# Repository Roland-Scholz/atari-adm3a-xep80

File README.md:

# atari-adm3a-xep80
ADM-3A Terminal for ATR8000 and XEP80

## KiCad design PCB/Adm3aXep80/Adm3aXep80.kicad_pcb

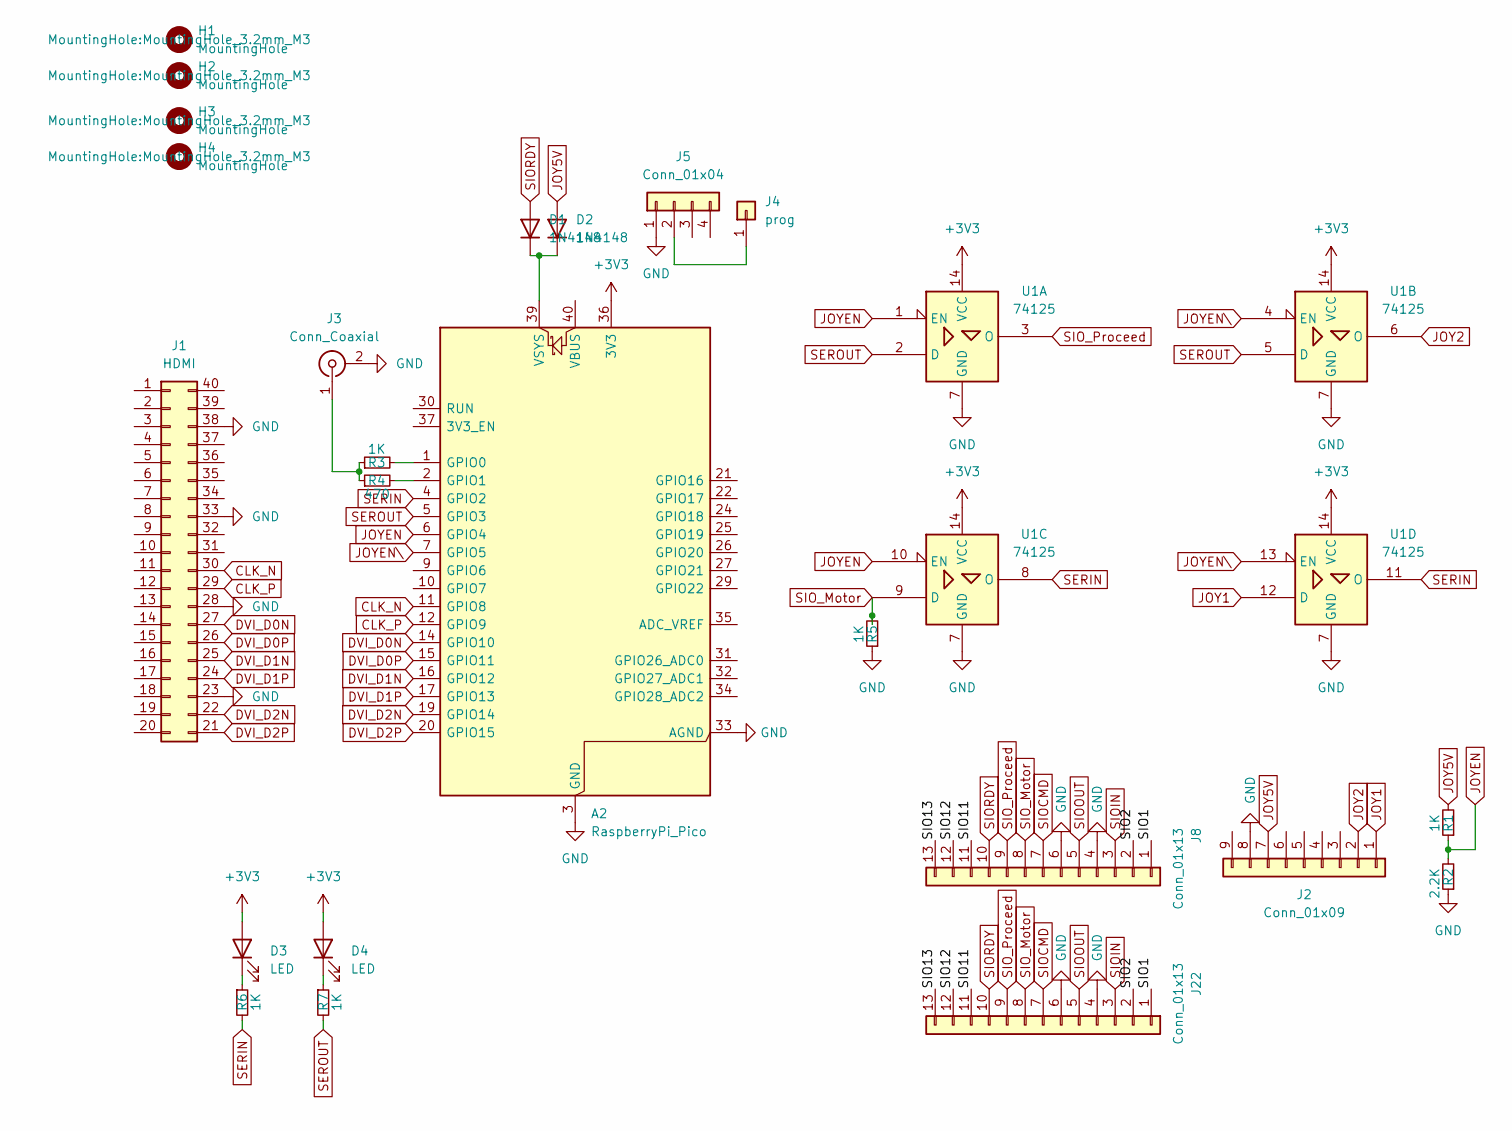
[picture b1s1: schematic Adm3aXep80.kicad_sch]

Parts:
A2: RaspberryPi_Pico; RaspberryPi_Pico_Common_Unspecified
D1, D2: 1N4148; D_DO-35_SOD27_P7.62mm_Horizontal
D3, D4: LED; LED_D3.0mm
H1, H2, H3, H4: MountingHole; MountingHole_3.2mm_M3
J1: HDMI; DIP-40_W25.4mm_Socket_LongPads
J2: Conn_01x09; DSUB-9_Pins_Horizontal_P2.77x2.84mm_EdgePinOffset4.94mm_Hou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
J3: Conn_Coaxial; RCA-Phono_CUI-Devices_RCJ-01X_Horizontal
J4: prog; PinHeader_1x01_P2.54mm_Vertical
J5: Conn_01x04; SW_Tactile_SKHH_Angled
J8, J22: Conn_01x13; SIO_JACK
R1, R3, R5, R6, R7: 1K; R_Axial_DIN0207_L6.3mm_D2.5mm_P10.16mm_Horizontal
R2: 2.2K; R_Axial_DIN0207_L6.3mm_D2.5mm_P10.16mm_Horizontal
R4: 470; R_Axial_DIN0207_L6.3mm_D2.5mm_P10.16mm_Horizontal
U1: 74125; DIP-14_W7.62mm_Socket

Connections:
+3V3: A2.36 (3V3), D3.2 (A), D4.2 (A), U1.14 (VCC)
/SIO1: J8.1, J22.1
/SIO2: J8.2, J22.2
/SIO11: J8.11, J22.11
/SIO12: J8.12, J22.12
/SIO13: J8.13, J22.13
CLK_N: A2.11 (GPIO8), J1.30
CLK_P: A2.12 (GPIO9), J1.29
DVI_D0N: A2.14 (GPIO10), J1.27
DVI_D0P: A2.15 (GPIO11), J1.26
DVI_D1N: A2.16 (GPIO12), J1.25
DVI_D1P: A2.17 (GPIO13), J1.24
DVI_D2N: A2.19 (GPIO14), J1.22
DVI_D2P: A2.20 (GPIO15), J1.21
GND: A2.3 (GND), A2.8 (GND), A2.13 (GND), A2.18 (GND), A2.23 (GND), A2.28 (GND), A2.33 (AGND), A2.38 (GND), J1.23, J1.28, J1.33, J1.38, J2.8, J3.2 (Ext), J5.1, J8.4, J8.6, J22.4, J22.6, R2.1, R5.1, U1.7 (GND)
JOY1: J2.1, U1.12 (D)
JOY2: J2.2, U1.6 (O)
JOY5V: D2.2 (A), J2.7, R1.2
JOYEN: A2.6 (GPIO4), R1.1, R2.2, U1.1 (EN), U1.10 (EN)
JOYEN\: A2.7 (GPIO5), U1.4 (EN), U1.13 (EN)
unnamed: A2.1 (GPIO0), R3.2
unnamed: A2.2 (GPIO1), R4.2
unnamed: A2.39 (VSYS), D1.1 (K), D2.1 (K)
unnamed: D3.1 (K), R6.1
unnamed: D4.1 (K), R7.1
unnamed: J3.1 (In), R3.1, R4.1
unnamed: J4.1, J5.2
SERIN: A2.4 (GPIO2), R6.2, U1.8 (O), U1.11 (O)
SEROUT: A2.5 (GPIO3), R7.2, U1.2 (D), U1.5 (D)
SIOCMD: J8.7, J22.7
SIOIN: J8.3, J22.3
SIOOUT: J8.5, J22.5
SIORDY: D1.2 (A), J8.10, J22.10
SIO_Motor: J8.8, J22.8, R5.2, U1.9 (D)
SIO_Proceed: J8.9, J22.9, U1.3 (O)

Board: 2 copper layers, 24 parts (0 on the bottom side), 35 nets, no tracks yet.

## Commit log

2025-06-03 comments
2025-06-05 ADM-3A stuff nearly complete
2025-08-11 first working Joy + SIO
2025-08-15 SIO working with original driver
2025-08-19 Bobterm - work in progress
2025-08-19 bobterm wip
2025-08-19 SIO PiXEP-80 working!
2025-09-01 KiCad PCB
2025-09-20 Joy + SIO
2025-09-21 vt100
2025-10-03 bugfix, SIO working etc.
2025-10-29 rework release
